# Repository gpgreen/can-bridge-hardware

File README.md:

# Can-Bridge

Kicad design for a CAN to USB serial bridge. Based on a Nucleo-F103RB development board
with an arduino shield that provides the CAN transceiver for the CAN
controller that resides on the STM32F103RB device on the dev board.

## CAN Hardware

The CAN controller on the Nucleo dev board, is routed to a MCP2551 transceiver on the
arduino daughter board. The two CAN outputs from the transceiver go to the CAN1 connector on
the daughter board. This connector is pinned:

```
 +---+
 | o | NC
[| o | CANH
[| o | CANL
 | o | NC
 +---+
  CAN1
```

A 120 ohm terminating resistor is also on the board. To use this resistor, set the DIP switch
position 1 to on.

## Firmware

The firmware is designed to be used with Serial CAN from the canutils project. Rust-based  project.

## Schematics

## Development Board

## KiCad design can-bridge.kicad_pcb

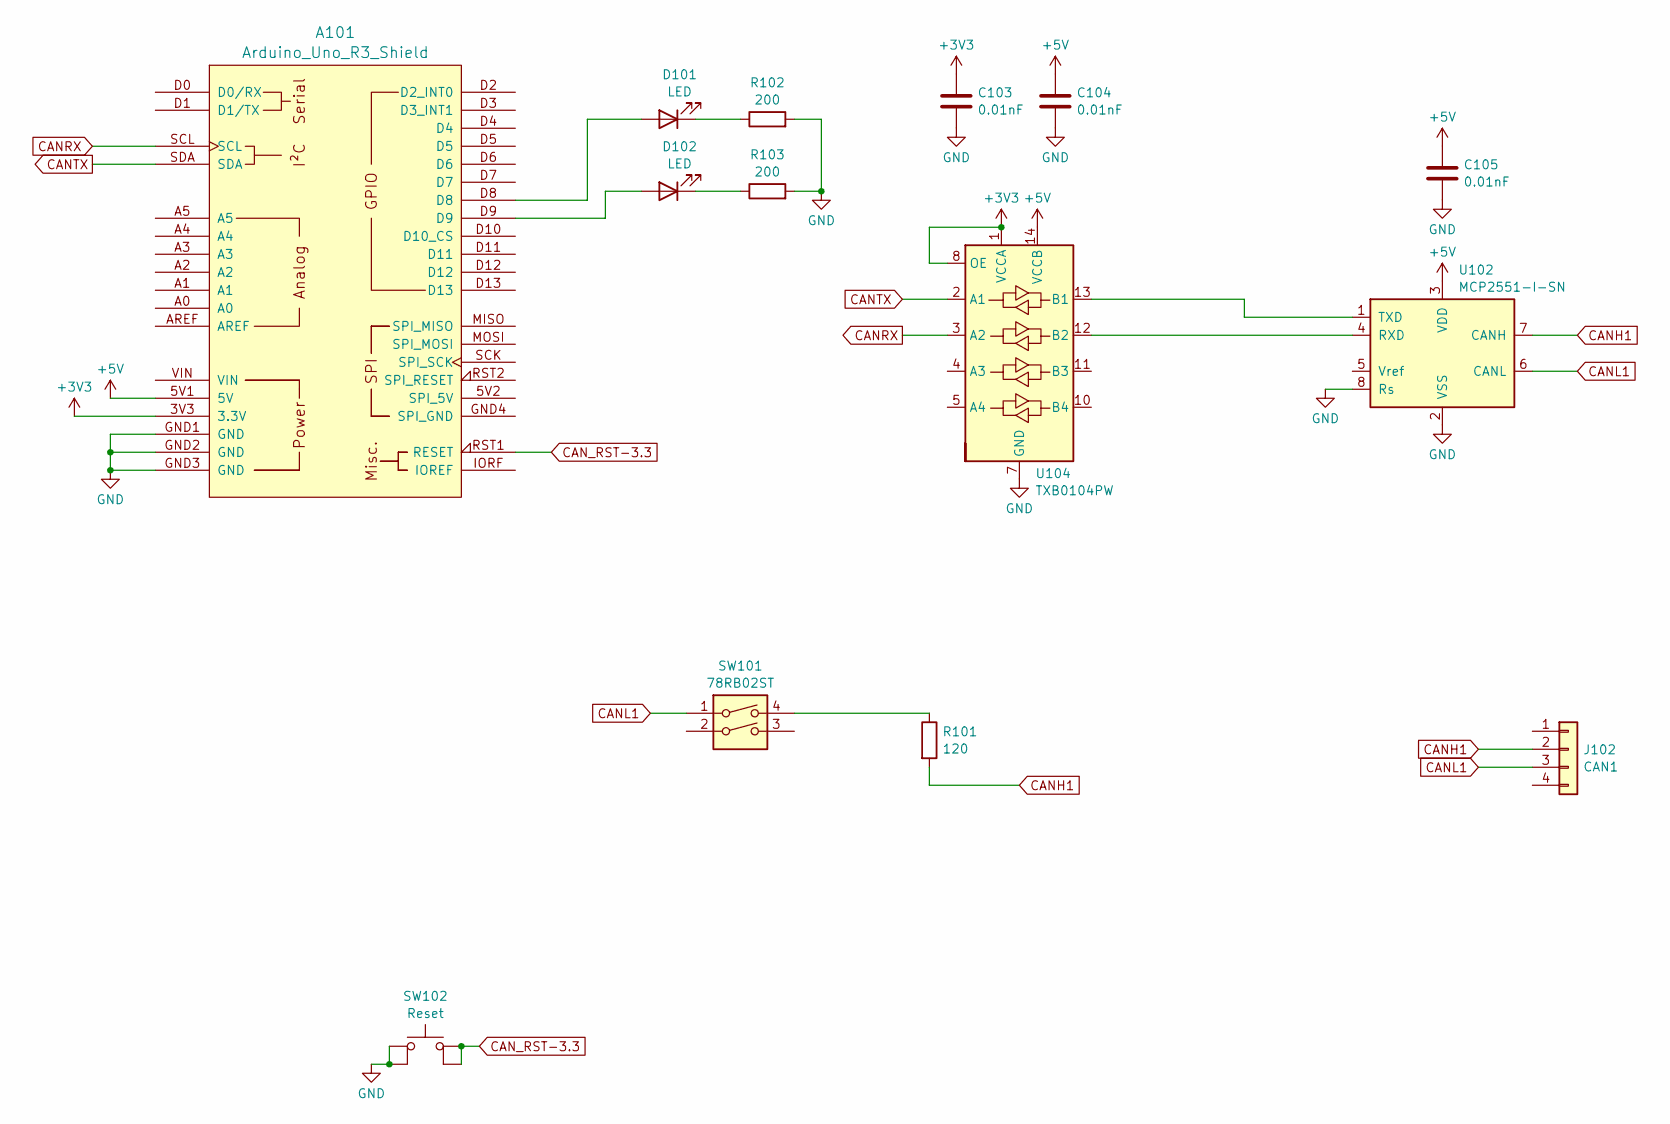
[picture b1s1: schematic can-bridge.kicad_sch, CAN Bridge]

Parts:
A101: Arduino_Uno_R3_Shield
C103, C104, C105: 0.01nF; C_0603_1608Metric
D101, D102: LED; LED_0603_1608Metric
J102: CAN1; JST_EH_B4B-EH-A_1x04_P2.50mm_Vertical
R101: 120; R_1206_3216Metric
R102, R103: 200; R_0603_1608Metric
SW101: 78RB02ST; SW_DIP_SPSTx02_Slide_9.78x7.26mm_W7.62mm_P2.54mm
SW102: Reset; OnShine KPT-1187B
U102: MCP2551-I-SN; SOIC-8_3.9x4.9mm_P1.27mm
U104: TXB0104PW; TSSOP-14_4.4x5mm_P0.65mm

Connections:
+3V3: A101.3V3 (3.3V), C103.1, U104.1 (VCCA), U104.8 (OE)
+5V: A101.5V1 (5V), C104.1, C105.1, U102.3 (VDD), U104.14 (VCCB)
CANH1: J102.2, R101.2, U102.7 (CANH)
CANL1: J102.3, SW101.1, U102.6 (CANL)
CANRX: A101.SCL, U104.3 (A2)
CANTX: A101.SDA, U104.2 (A1)
CAN_RST-3.3: A101.RST1 (RESET), SW102.2, SW102.4
GND: A101.GND1 (GND), A101.GND2 (GND), A101.GND3 (GND), C103.2, C104.2, C105.2, R102.2, R103.2, SW102.1, SW102.3, U102.2 (VSS), U102.8 (Rs), U104.7 (GND)
unnamed: A101.D8, D101.2 (A)
unnamed: D101.1 (K), R102.1
unnamed: A101.D9, D102.2 (A)
unnamed: D102.1 (K), R103.1
unnamed: R101.1, SW101.4
unnamed: U102.4 (RXD), U104.12 (B2)
unnamed: U102.1 (TXD), U104.13 (B1)

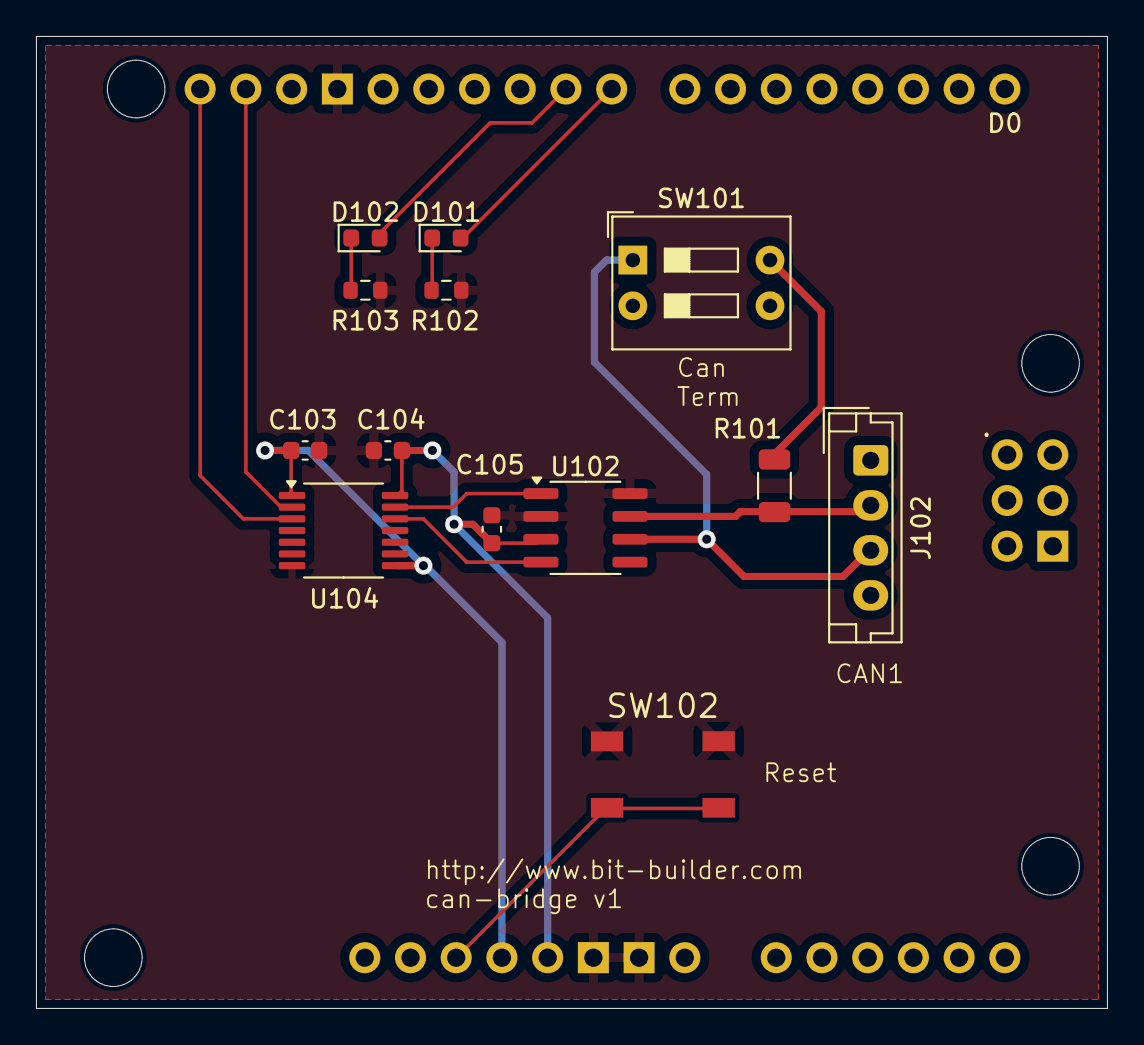
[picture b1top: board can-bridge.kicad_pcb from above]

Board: 2 copper layers, 59.5 x 54.0 mm, 14 parts (0 on the bottom side), 15 nets.

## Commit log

2024-04-26 Added README.md and image of prototype
    Changed R101 resistor to 1206 footprint
2024-04-26 Forgot code quotes in README.md
